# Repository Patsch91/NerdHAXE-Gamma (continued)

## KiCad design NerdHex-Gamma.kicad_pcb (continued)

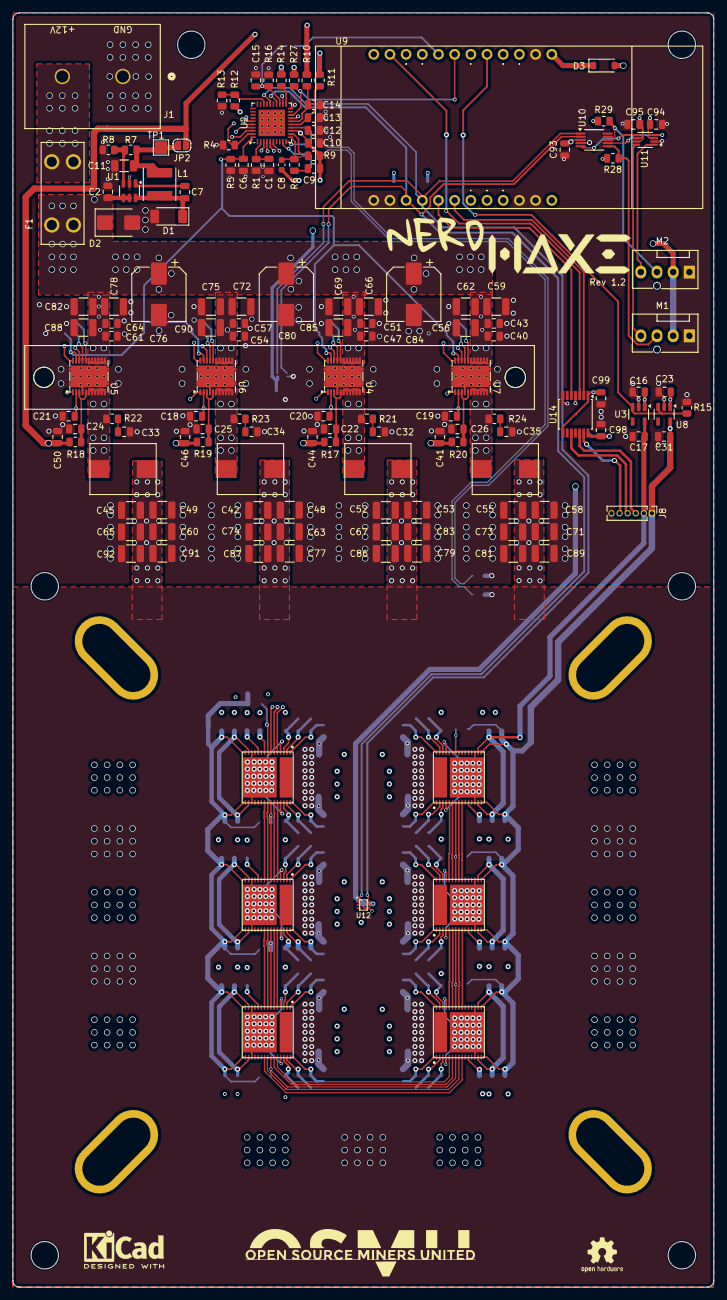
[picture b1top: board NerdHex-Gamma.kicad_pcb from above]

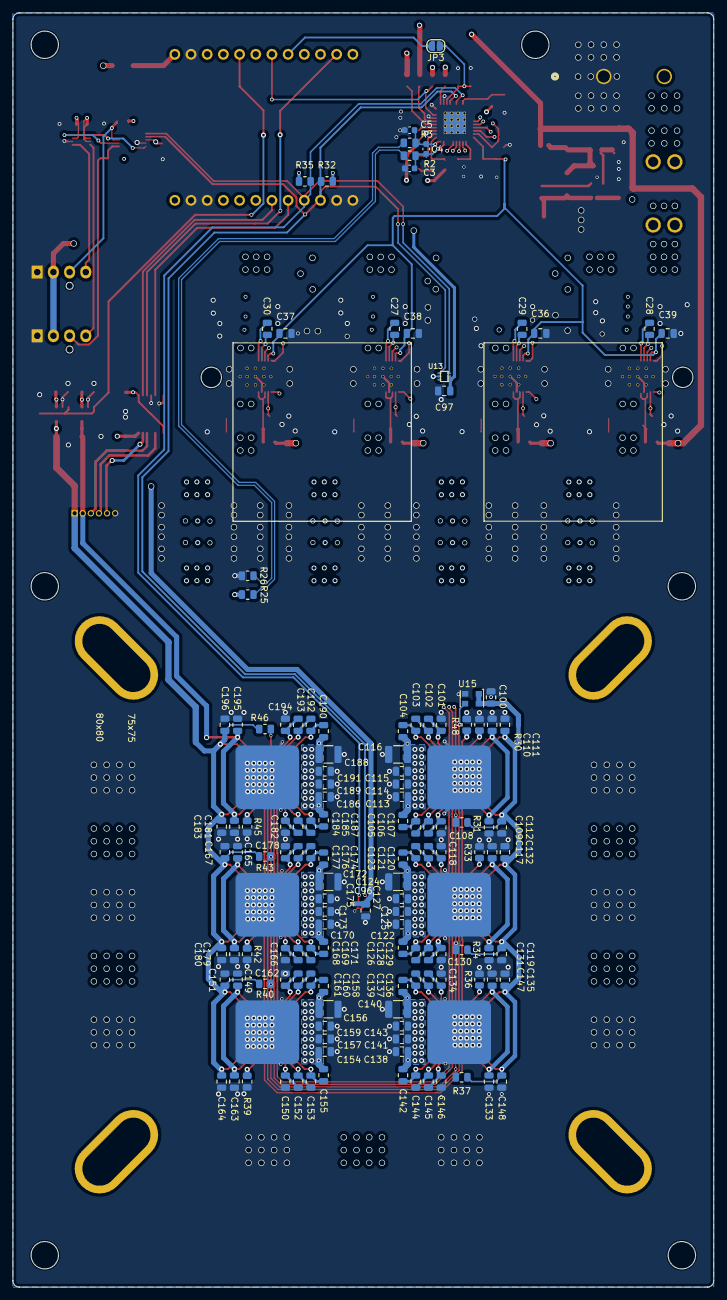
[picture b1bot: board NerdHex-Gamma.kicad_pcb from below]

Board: 6 copper layers, 110.0 x 200.0 mm, 275 parts (132 on the bottom side), 145 nets.

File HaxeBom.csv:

"Reference","Value","Footprint","OrderNr","Qty","DNP","Distributor"
"C1","2.2n","Capacitor_SMD:C_0805_2012Metric","1276-2993-1-ND","1","","D"
"C2,C41,C44,C46,C50,C113,C122,C138,C154,C170,C186","10µ/25V","Capacitor_SMD:C_0805_2012Metric","445-5984-1-ND","11","","D"
"C3,C4,C5","22p","Capacitor_SMD:C_0603_1608Metric","478-KGM15ACG1H220JTCT-ND","3","","D"
"C6,C9,C15,C32,C33,C34,C35,C36,C37,C38,C39","1n/0.7mm","Capacitor_SMD:C_0805_2012Metric","311-1472-1-ND","11","","D"
"C7","10n","Capacitor_SMD:C_0805_2012Metric","732-8021-1-ND","1","","D"
"C8","12p","Capacitor_SMD:C_0603_1608Metric","478-KGM15ACG2A120JMCT-ND","1","","D"
"C10","330n","Capacitor_SMD:C_0805_2012Metric","399-C0805C334K3RECAUTOCT-ND","1","","D"
"C11","22µ/16V","Capacitor_SMD:C_1206_3216Metric","1276-2728-1-ND","1","","D"
"C12,C14,C17,C31,C43,C51,C57,C64,C101,C102,C103,C104,C105,C106,C107,C108,C109,C110,C111,C112,C114,C117,C118,C119,C120,C121,C123,C125,C126,C128,C129,C130,C131,C132,C133,C134,C135,C136,C137,C139,C141,C142,C144,C145,C146,C147,C148,C149,C150,C151,C152,C153,C155,C157,C158,C160,C161,C162,C163,C164,C165,C166,C167,C168,C169,C171,C173,C174,C176,C177,C178,C179,C180,C181,C182,C183,C184,C185,C187,C189,C190,C192,C193,C194,C195,C196","1µ/25V","Capacitor_SMD:C_0805_2012Metric","1276-1066-1-ND","86","","D"
"C13","4.7µ","Capacitor_SMD:C_0805_2012Metric","1276-1244-1-ND","1","","D"
"C16,C18,C19,C20,C21,C23,C27,C28,C29,C30,C93,C94,C95,C96,C97,C98,C99,C100,C115,C127,C143,C159,C175,C191","100n/0.7mm","Capacitor_SMD:C_0805_2012Metric","311-3037-1-ND","24","","D"
"C22,C24,C25,C26","2.2µ","Capacitor_SMD:C_0805_2012Metric","1276-6458-1-ND","4","","D"
"C40,C47,C54,C61","3.3n/25V","Capacitor_SMD:C_0805_2012Metric","490-8291-1-ND","4","","D"
"C42,C45,C48,C49,C52,C53,C55,C58,C116,C124,C140,C156,C172,C188","100µ/6.3V","Capacitor_SMD:C_1210_3225Metric","399-C1210C107M8PAC7800CT-ND","14","","D"
"C56,C59,C62,C66,C69,C72,C75,C78,C82,C85,C88,C90","22µ/25V","Capacitor_SMD:C_1210_3225Metric","399-C1210C226K3PAC7800CT-ND","12","","D"
"C60,C63,C65,C67,C68,C70,C71,C73,C74,C77,C79,C81,C83,C86,C87,C89,C91,C92","330µ/4V","Capacitor_SMD:C_1210_3225Metric","490-GRM32ER60G337ME05KCT-ND","18","","D"
"C76,C80,C84","220µ/25V","Capacitor_SMD:CP_Elec_8x10","732-6489-1-ND","3","","D"
"D1","PMEG4030EP,115","Diode_SMD:D_SOD-128","1727-5841-1-ND","1","","D"
"D2","SMBJ12A","Diode_SMD:D_SMB","SMBJ12ALFCT-ND","1","","D"
"D3","1N5819","Diode_SMD:D_SOD-123","31-1N5819HWQ-7-FCT-ND","1","","D"
"F1","3568","8Axe:Fuseholder Blade_3568","36-3568-ND","1","","D"
"H1","Threaded Inserts","","36-24949CT-ND","1","","D"
"J1","Connector 02x01","Nerd8:CONN2","ED2953-ND","1","","D"
"J4,J5","Conn_01x12-Socket","","732-61301211821-ND","2","","D"
"J6,J7","Conn_01x12-Header","","2057-PH1-12-UA-ND","2","","D"
"L1","4.7µH/2.3A/2.7A","Inductor_SMD:L_Taiyo-Yuden_NR-50xx","732-7244-1-ND","1","","D"
"L2,L3,L4,L5","220nH","myfootprints:IFLR-4031GC-01-8x10","283-FP1008R5-R220-RCT-ND","4","","D"
"M1,M2","Fan_4pin","Connector:FanPinHeader_1x04_P2.54mm_Vertical","WM4330-ND","2","","D"
"R1","49.9k","Resistor_SMD:R_0805_2012Metric","311-49.9KCRCT-ND","1","","D"
"R2,R3","100","Resistor_SMD:R_0805_2012Metric","311-100CRCT-ND","2","","D"
"R4","100k","Resistor_SMD:R_0805_2012Metric","RMCF0805FT100KCT-ND","1","","D"
"R5","121k","Resistor_SMD:R_0805_2012Metric","RMCF0805FT121KCT-ND","1","","D"
"R6","8.06k","Resistor_SMD:R_0805_2012Metric","RMCF0805FT8K06CT-ND","1","","D"
"R7","84.5k","Resistor_SMD:R_0805_2012Metric","311-84.5KCRCT-ND","1","","D"
"R8","16.2k","Resistor_SMD:R_0805_2012Metric","RMCF0805FT16K2CT-ND","1","","D"
"R9","2.55k","Resistor_SMD:R_0805_2012Metric","311-2.55KCRCT-ND","1","","D"
"R10,R11","2.2R/0.5W","Resistor_SMD:R_0805_2012Metric","541-10524-1-ND","2","","D"
"R12","16.5k","Resistor_SMD:R_0805_2012Metric","541-16.5KCCT-ND","1","","D"
"R13","24.3k","Resistor_SMD:R_0805_2012Metric","311-24.3KCRCT-ND","1","","D"
"R14,R15,R16,R27,R31,R34,R37,R40,R43,R46,R48","10k","Resistor_SMD:R_0805_2012Metric","RMCF0805FT10K0CT-ND","11","","D"
"R17,R18,R19,R20,R21,R22,R23,R24","1R/0.5W","Resistor_SMD:R_0805_2012Metric","541-1.00TCT-ND","8","","D"
"R25,R26,R32,R35","0","Resistor_SMD:R_0805_2012Metric","RMCF0805ZT0R00CT-ND","4","","D"
"R28,R29","2.7k","Resistor_SMD:R_0805_2012Metric","RMCF0805FT2K70CT-ND","2","","D"
"R30,R33,R36,R39,R42,R45","1k","Resistor_SMD:R_0805_2012Metric","RNCP0805FTD1K00CT-ND","6","","D"
"U1","AP3211","Package_TO_SOT_SMD:SOT-23-6","AP3211KTR-G1DICT-ND","1","","D"
"U2","TPS53647","Package_DFN_QFN:Texas_RHA0040B_VQFN-40-1EP_6x6mm_P0.5mm_EP4.15x4.15mm_ThermalVias","296-51986-1-ND","1","","D"
"U3","MCP1824T-0802E","Package_TO_SOT_SMD:SOT-23-5","MCP1824T-0802E/OTCT-ND","1","","D"
"U4,U5,U6,U7","CSD95472Q5MC","myfootprints:CSD95472-SON-5x6","296-43950-1-ND","4","","D"
"U8","MCP1824T-1202E","Package_TO_SOT_SMD:SOT-23-5","MCP1824T-1202E/OTCT-ND","1","","D"
"U9","T-Display-S3","myfootprints:T-Display-S3","","1","Nicht bestücken",""
"U10","EMC2302-1","Package_SO:MSOP-10_3x3mm_P0.5mm","EMC2302-1-AIZL-CT-ND","1","","D"
"U11","TXU0102-DCU","Package_SO:VSSOP-8_2.3x2mm_P0.5mm","296-TXU0102DCURCT-ND","1","","D"
"U12,U13","TMP1075","Qaxe:TMP1075-DRL","296-TMP1075NDRLRCT-ND","2","","D"
"U14","TXU0304PW","Package_SO:TSSOP-14-1EP_4.4x5mm_P0.65mm","296-TXU0304PWRCT-ND","1","","D"
"U15","25MHz","Oscillator:Oscillator_SMD_EuroQuartz_XO32-4Pin_3.2x2.5mm","1923-1664-1-ND","1","","D"
"U16,U17,U18,U19,U20,U21","BM1370_mode1","Nerd8:BM1370","","6","",""

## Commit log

2025-01-16 schematic
2025-01-19 test
2025-01-19 asictest
2025-01-19 fail
2025-01-19 Asic
2025-01-19 asic2
2025-01-19 asic3
2025-01-19 asic4
2025-01-20 review
2025-01-21 buck
2025-01-21 puuuuuh
2025-01-22 Sense1-2
2025-01-23 plated slots
2025-01-26 2601
2025-02-02 0202
2025-02-23 added iBom
2025-02-23 Ignore Backups
2025-02-23 DK Bom
2025-02-23 add images
2025-02-23 added images
2025-03-14 Bucktest 90
2025-03-14 Testrouting
2025-03-14 80x10
2025-03-15 DRC GND Vias
2025-03-15 case
2025-03-16 1603
2025-03-17 1703
2025-03-20 vias drc
2025-04-30 3004
2025-05-01 connected 12V Input
2025-05-02 12V Input + i2c pullups
2025-07-21 2,7k Pull ups
